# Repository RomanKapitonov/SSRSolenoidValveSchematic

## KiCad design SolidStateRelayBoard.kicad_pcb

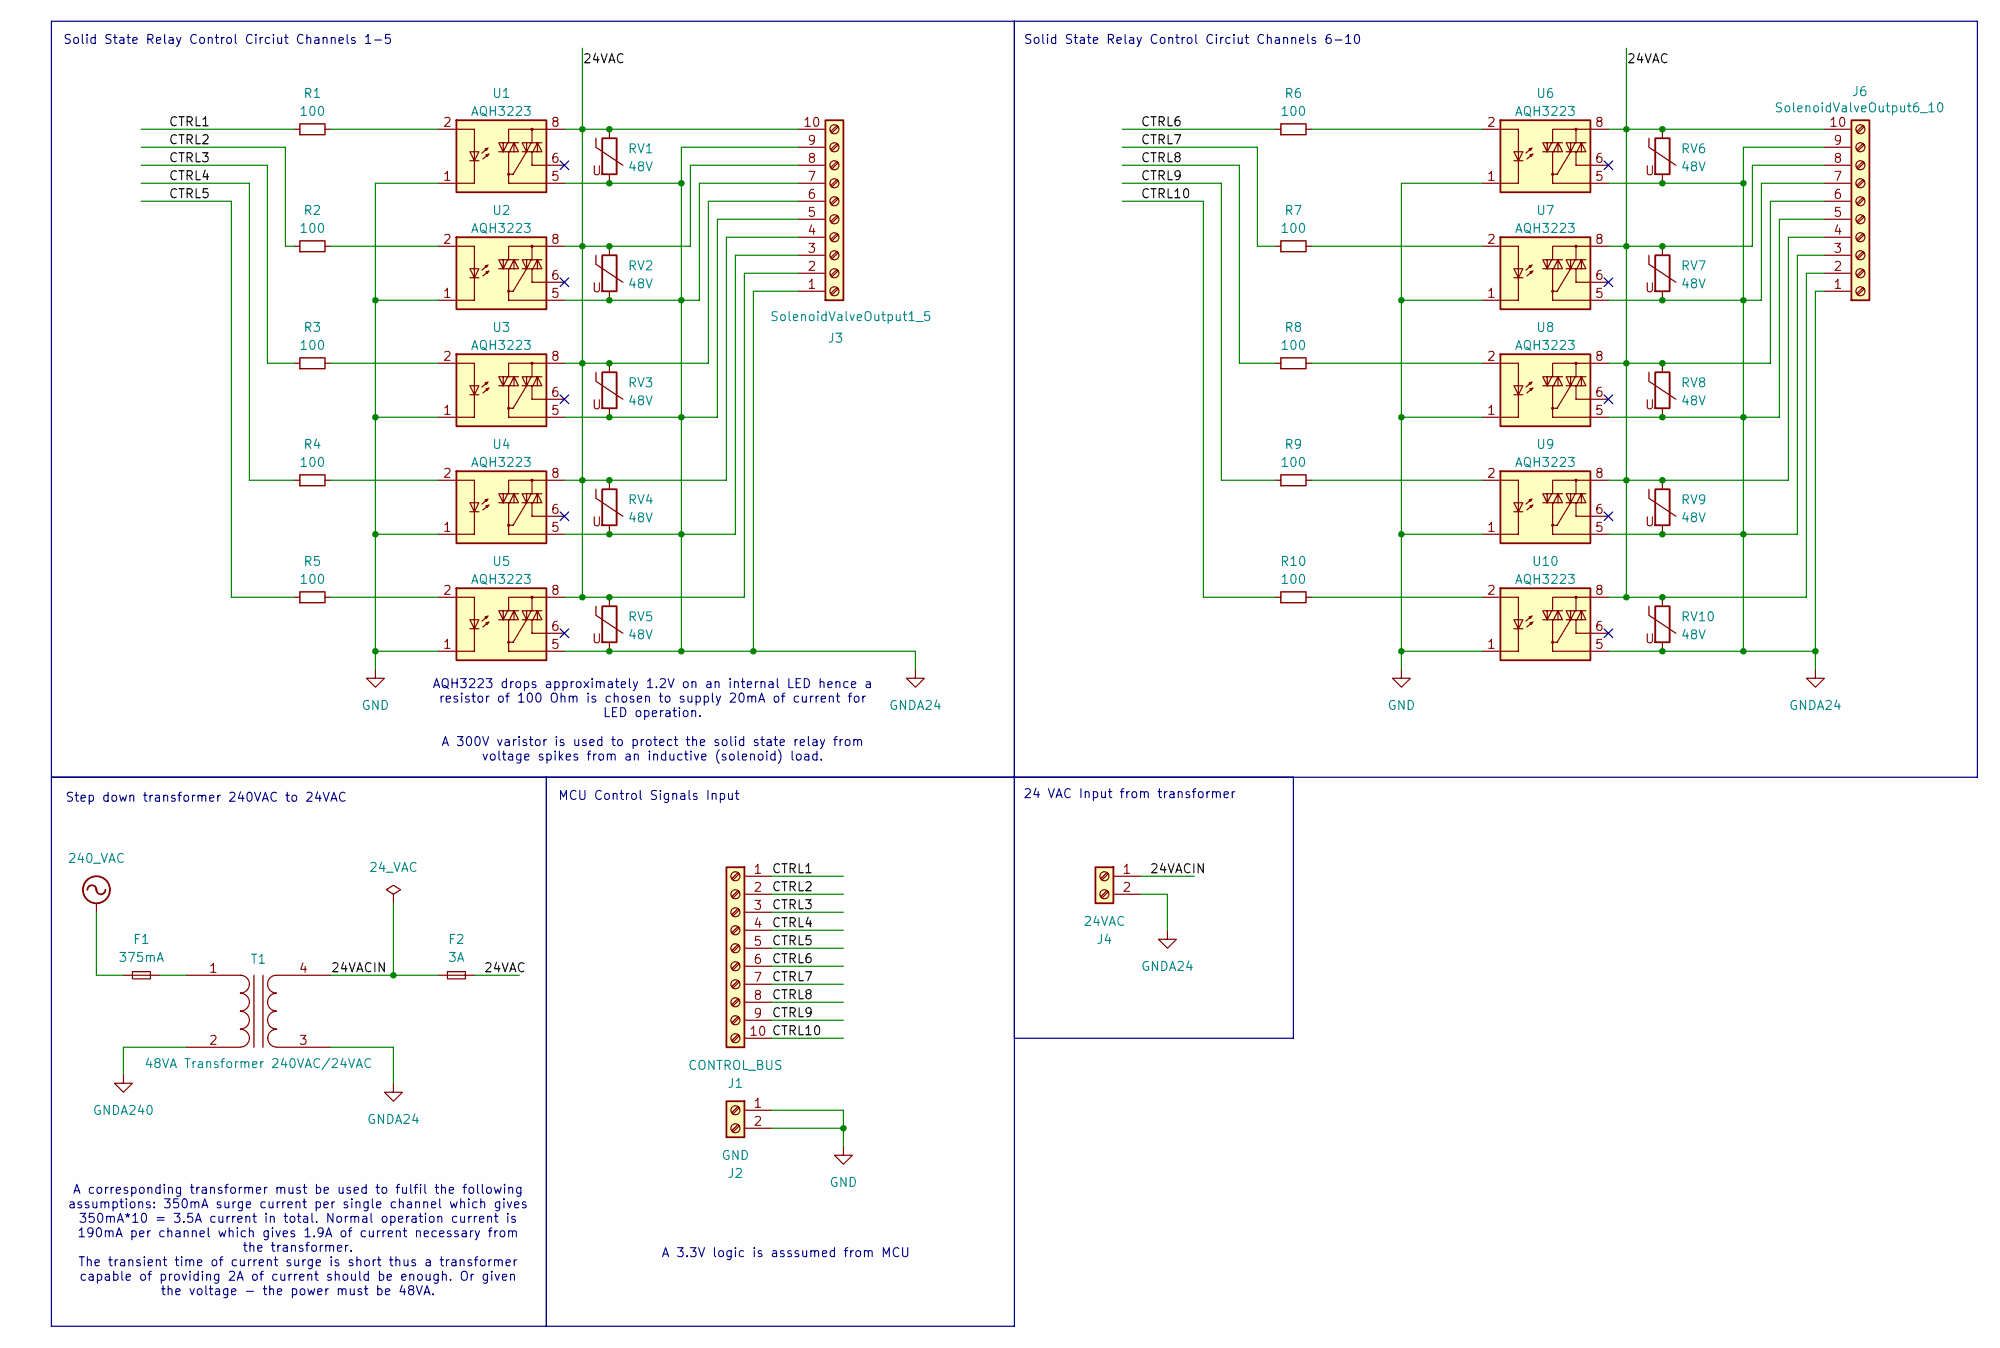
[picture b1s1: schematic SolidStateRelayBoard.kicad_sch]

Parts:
F1: 375mA; Fuseholder_Clip-5x20mm_Eaton_1A5601-01_Inline_P20.80x6.76mm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
F2: 3A; Fuseholder_Cylinder-5x20mm_Schurter_0031_8201_Horizontal_Op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
J1: CONTROL_BUS; TerminalBlock_Xinya_XY308-2.54-10P_1x10_P2.54mm_Horizontal
J2: GND; TerminalBlock_Xinya_XY308-2.54-2P_1x02_P2.54mm_Horizontal
J3: SolenoidValveOutput1_5; TerminalBlock_4Ucon_1x10_P3.50mm_Horizontal
J4: 24VAC; TerminalBlock_4Ucon_1x02_P3.50mm_Horizontal
J6: SolenoidValveOutput6_10; TerminalBlock_4Ucon_1x10_P3.50mm_Horizontal
R1, R2, R3, R4, R5, R6, R7, R8, R9, R10: 100; R_0805_2012Metric
RV1, RV2, RV3, RV4, RV5, RV6, RV7, RV8, RV9, RV10: 48V; RV_Disc_D12mm_W3.9mm_P7.5mm
T1: 48VA Transformer 240VAC/24VAC
U1, U2, U3, U4, U5, U6, U7, U8, U9, U10: AQH3223; DIP-8-N7_W7.62mm

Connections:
/24VAC: F2.2, J3.2, J3.4, J3.6, J3.8, J3.10, J6.2, J6.4, J6.6, J6.8, J6.10, RV1.1, RV2.1, RV3.1, RV4.1, RV5.1, RV6.1, RV7.1, RV8.1, RV9.1, RV10.1, U1.8, U2.8, U3.8, U4.8, U5.8, U6.8, U7.8, U8.8, U9.8, U10.8
/24VACIN: F2.1, J4.1, T1.4 (SB)
/CTRL1: J1.1, R1.1
/CTRL2: J1.2, R2.1
/CTRL3: J1.3, R3.1
/CTRL4: J1.4, R4.1
/CTRL5: J1.5, R5.1
/CTRL6: J1.6, R6.1
/CTRL7: J1.7, R7.1
/CTRL8: J1.8, R8.1
/CTRL9: J1.9, R9.1
/CTRL10: J1.10, R10.1
GND: J2.1, J2.2, U1.1, U1.3, U1.4, U2.1, U2.3, U2.4, U3.1, U3.3, U3.4, U4.1, U4.3, U4.4, U5.1, U5.3, U5.4, U6.1, U6.3, U6.4, U7.1, U7.3, U7.4, U8.1, U8.3, U8.4, U9.1, U9.3, U9.4, U10.1, U10.3, U10.4
GNDA24: J3.1, J3.3, J3.5, J3.7, J3.9, J4.2, J6.1, J6.3, J6.5, J6.7, J6.9, RV1.2, RV2.2, RV3.2, RV4.2, RV5.2, RV6.2, RV7.2, RV8.2, RV9.2, RV10.2, T1.3 (SA), U1.5, U2.5, U3.5, U4.5, U5.5, U6.5, U7.5, U8.5, U9.5, U10.5
unnamed: F1.2, T1.1 (AA)
unnamed: R1.2, U1.2
unnamed: R2.2, U2.2
unnamed: R3.2, U3.2
unnamed: R4.2, U4.2
unnamed: R5.2, U5.2
unnamed: R6.2, U6.2
unnamed: R7.2, U7.2
unnamed: R8.2, U8.2
unnamed: R9.2, U9.2
unnamed: R10.2, U10.2

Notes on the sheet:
MCU Control Signals Input
24 VAC Input from transformer
AQH3223 drops approximately 1.2V on an internal LED hence a resistor of 100 Ohm is chosen to supply 20mA of current for LED operation. A 300V varistor is used to protect the solid state relay from voltage spikes from an inductive (solenoid) load.
A corresponding transformer must be used to fulfil the following assumptions: 350mA surge current per single channel which gives 350mA*10 = 3.5A current in total. Normal operation current is 190mA per channel which gives 1.9A of current necessary from the transformer. The transient time of current 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
Step down transformer 240VAC to 24VAC
Solid State Relay Control Circiut Channels 6-10
A 3.3V logic is asssumed from MCU
Solid State Relay Control Circiut Channels 1-5

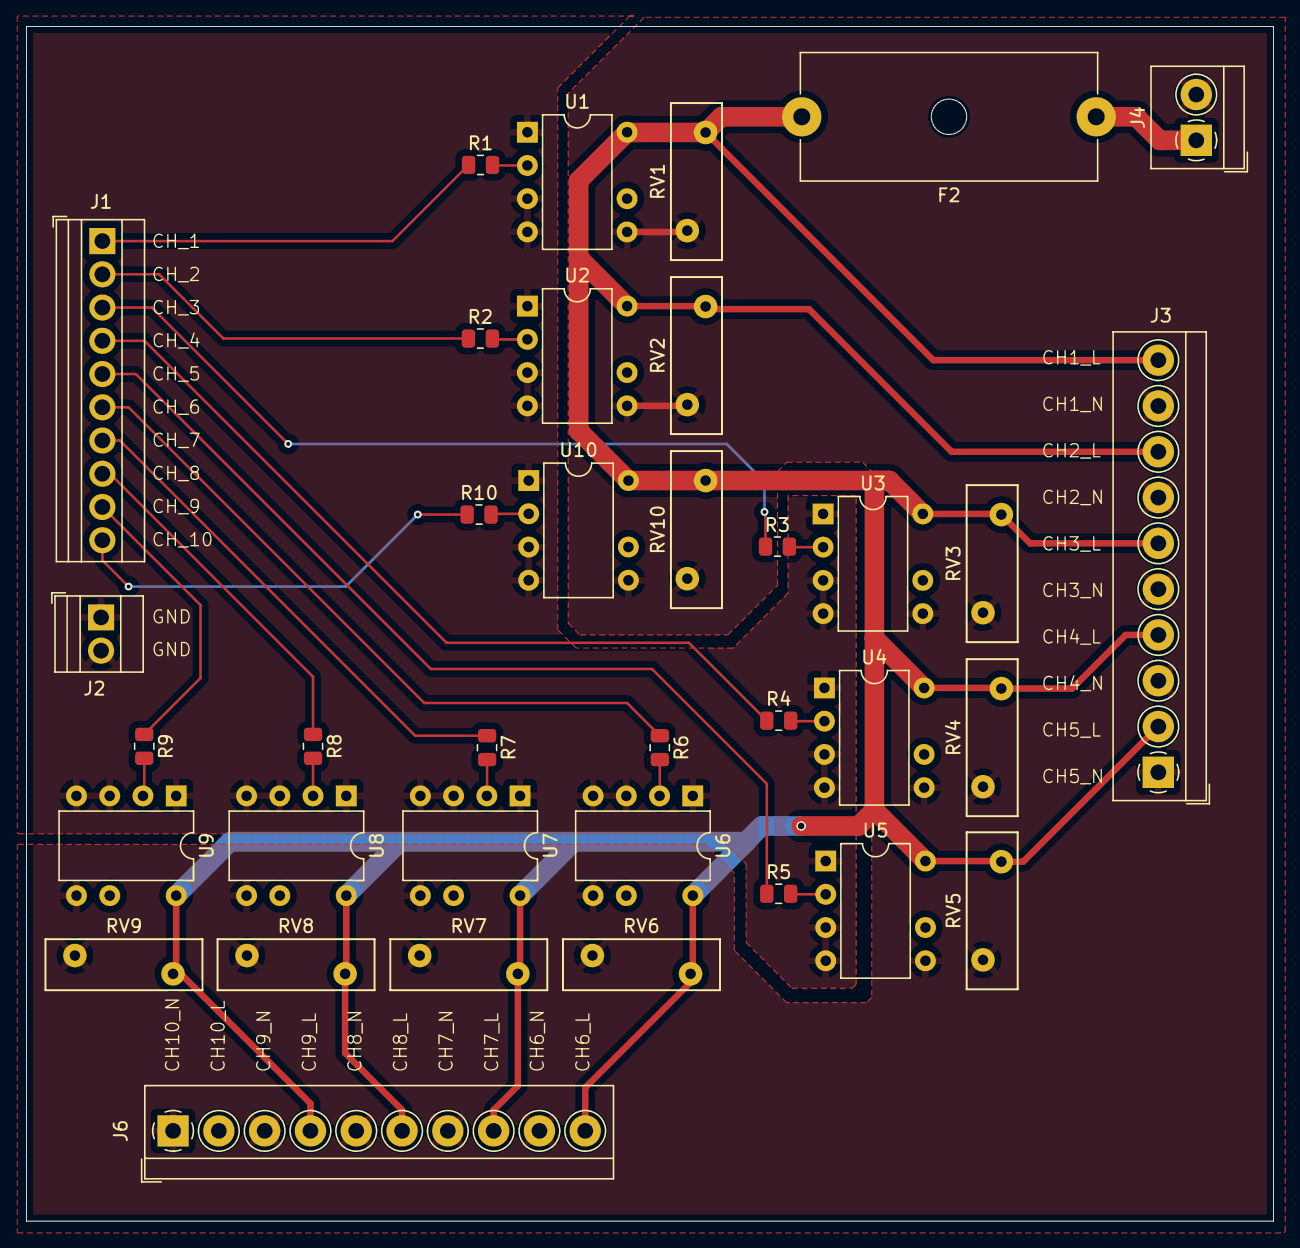
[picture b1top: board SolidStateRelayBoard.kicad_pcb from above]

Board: 2 copper layers, 95.3 x 91.3 mm, 36 parts (0 on the bottom side), 24 nets.

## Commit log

2024-08-03 Initial
2024-08-03 Add layout and 3D model
